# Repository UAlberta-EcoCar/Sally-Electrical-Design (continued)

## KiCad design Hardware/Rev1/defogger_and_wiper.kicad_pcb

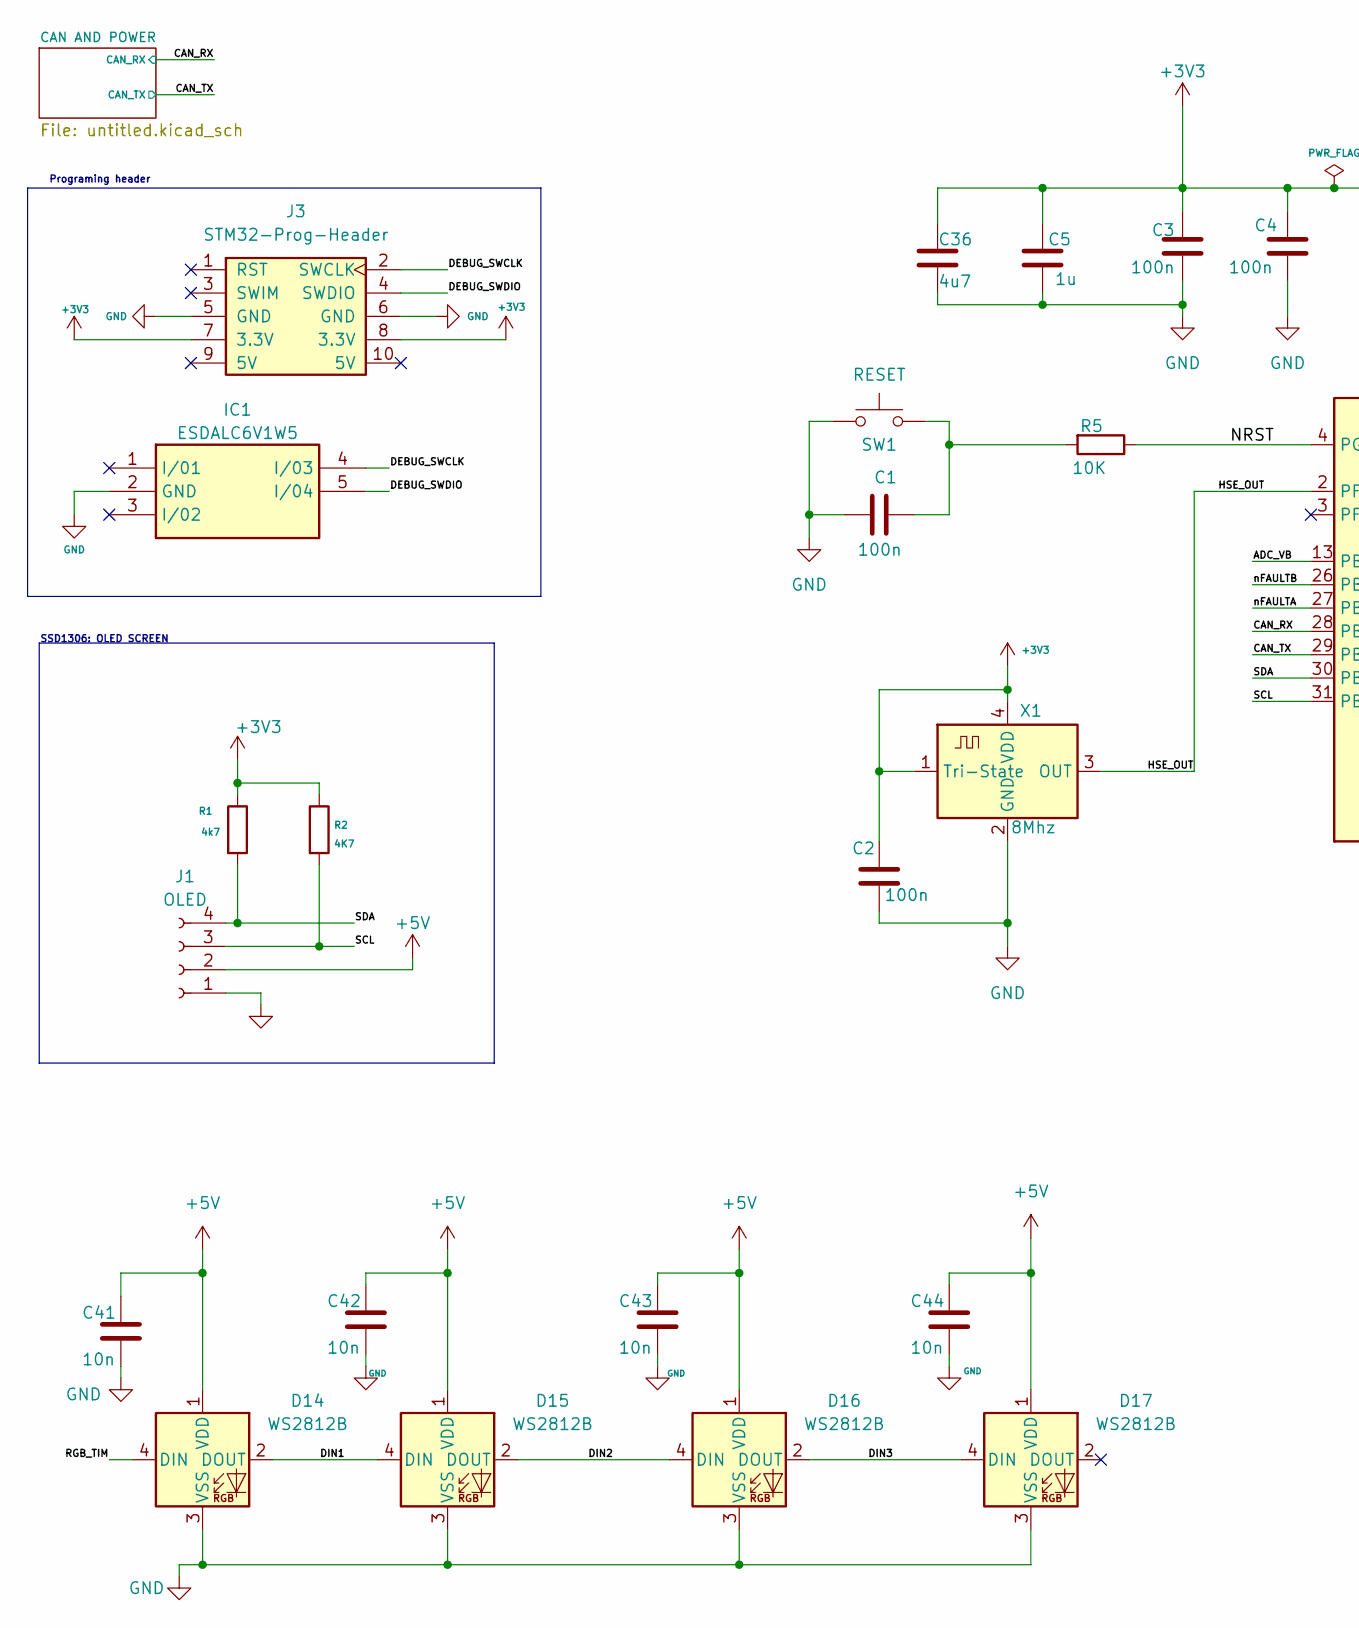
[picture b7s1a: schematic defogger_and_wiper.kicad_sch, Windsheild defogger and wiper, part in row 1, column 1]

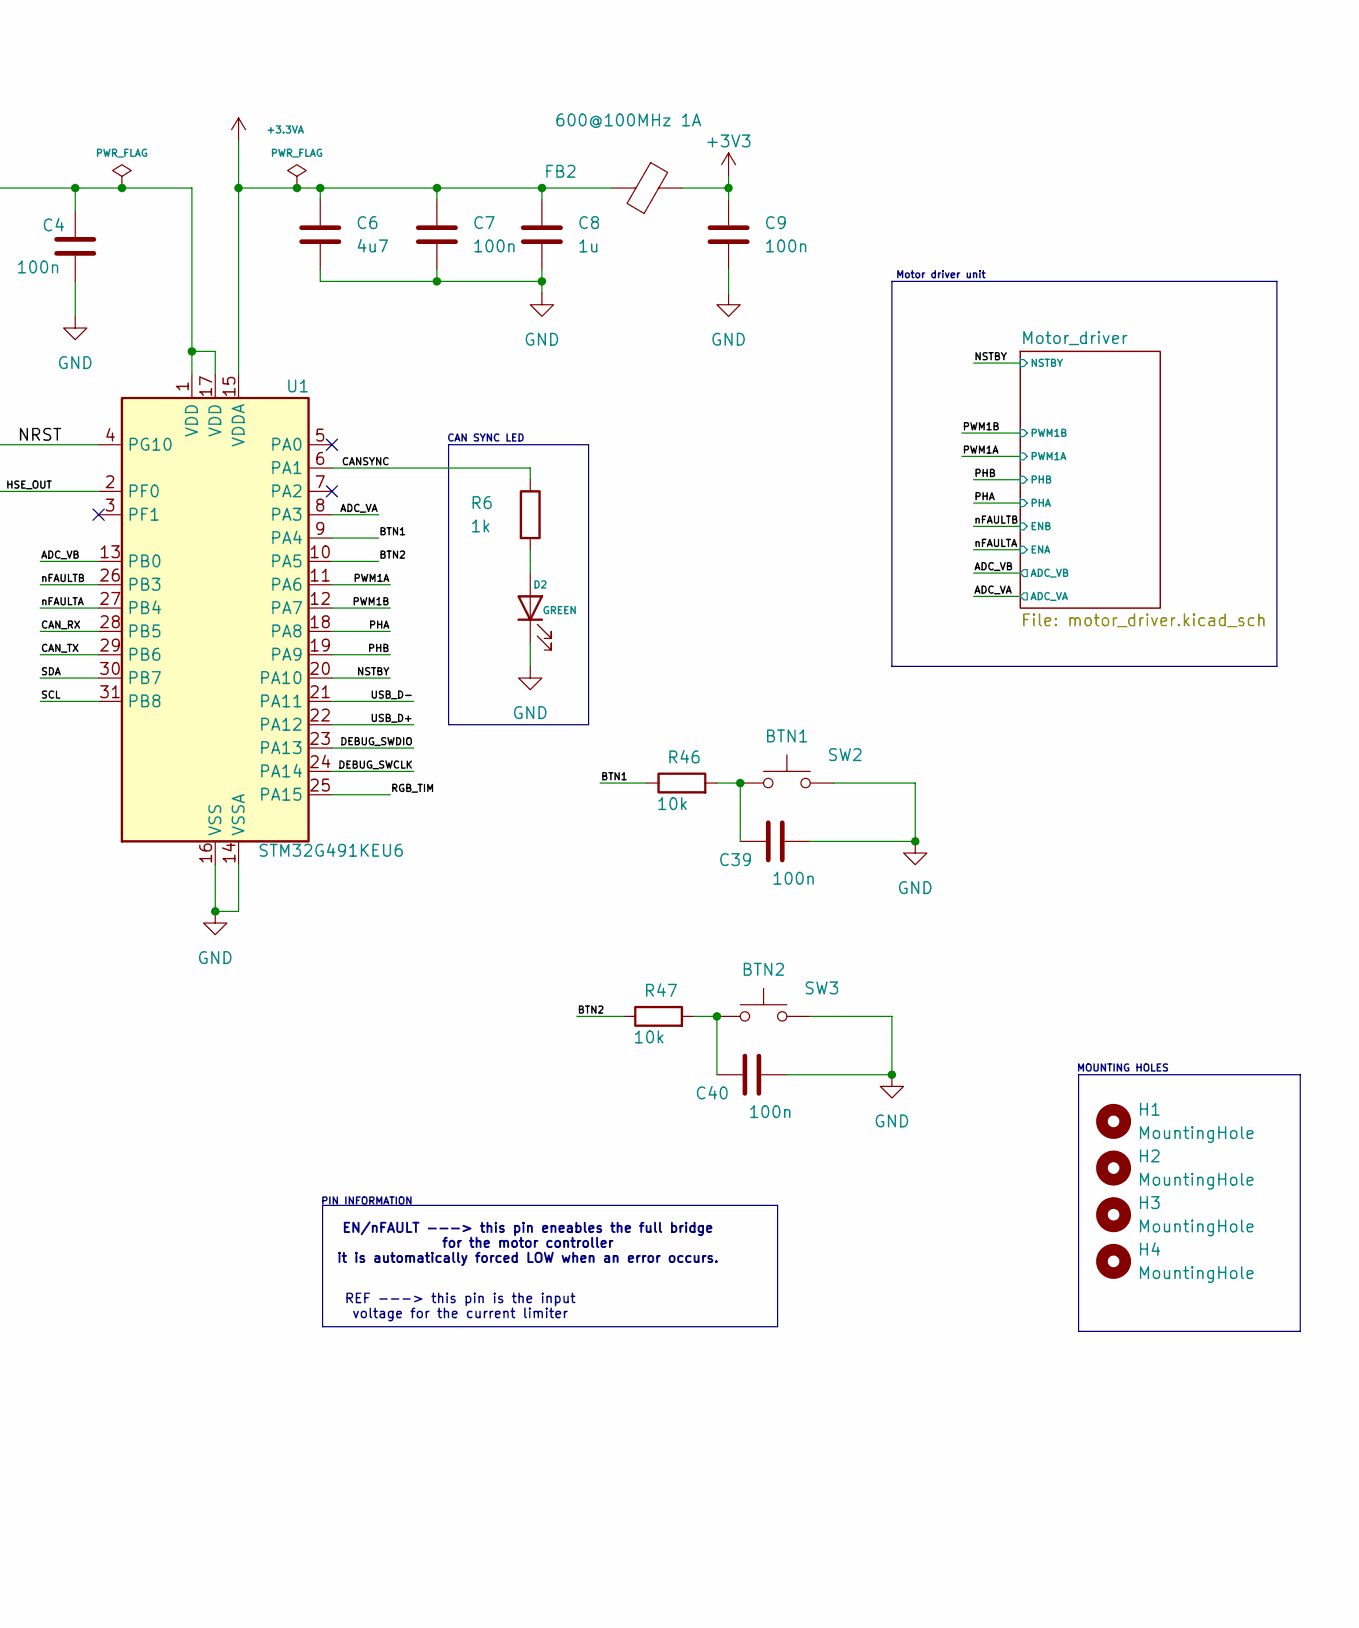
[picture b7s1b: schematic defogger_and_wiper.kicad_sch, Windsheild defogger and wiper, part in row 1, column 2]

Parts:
C1: 100n; C_0603_1608Metric; JLCPCB Part#(Optional) C1525
C2, C3, C4, C39, C40: 100n; C_0603_1608Metric
C5, C8: 1u; C_0603_1608Metric; JLCPCB Part#(Optional) C28323
C6, C36: 4u7; C_0603_1608Metric; JLCPCB Part#(Optional) C96446
C7: 100n; C_0603_1608Metric; JLCPCB Part#(Optional) C96446
C9: 100n; C_0603_1608Metric; JLCPCB Part#(Optional) C28323
C41, C42, C43, C44: 10n; C_0603_1608Metric; LCSC# C100042
D2: GREEN; LED_0603_1608Metric; LCSC# C19273151
D14, D15, D16, D17: WS2812B; LED_WS2812B_PLCC4_5.0x5.0mm_P3.2mm
FB2: 600@100MHz 1A; L_0603_1608Metric; Digikey # 1934-1474-1-ND
H1, H2, H3, H4: MountingHole; MountingHole_3.5mm
IC1: ESDALC6V1W5; SOT65P210X110-5N; JLCPCB Part#(Optional) C2827626
J1: OLED; Display_128x64_096_I2C
J3: STM32-Prog-Header; IDC-STM32-Prog-Header_2x05_P2.54mm_Vertical
R1: 4k7; R_0603_1608Metric
R2: 4K7; R_0603_1608Metric
R5: 10K; R_0603_1608Metric
R6: 1k; R_0603_1608Metric; LCSC# C21190
R46, R47: 10k; R_0603_1608Metric
SW1: RESET; SW_PUSH_6mm_H5mm
SW2: BTN1; SW_PUSH_6mm_H5mm
SW3: BTN2; SW_PUSH_6mm_H5mm
U1: STM32G491KEU6; QFN-32-1EP_5x5mm_P0.5mm_EP3.45x3.45mm
X1: 8Mhz; Crystal_SMD_3225-4Pin_3.2x2.5mm

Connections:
+3.3VA: C6.1, C7.1, C8.1, FB2.2, U1.15 (VDDA)
+3V3: C2.1, C3.1, C4.1, C5.1, C9.1, C36.1, FB2.1, J3.7 (3.3V), J3.8 (3.3V), R1.1, R2.1, U1.1 (VDD), U1.17 (VDD), X1.1 (Tri-State), X1.4 (VDD); also elsewhere on the board
+5V: C41.1, C42.1, C43.1, C44.1, D14.1 (VDD), D15.1 (VDD), D16.1 (VDD), D17.1 (VDD), J1.2; also elsewhere on the board
/ADC_VA: U1.8 (PA3); also elsewhere on the board
/ADC_VB: U1.13 (PB0); also elsewhere on the board
/BTN1: R46.1, U1.9 (PA4)
/BTN2: R47.1, U1.10 (PA5)
/CANSYNC: R6.1, U1.6 (PA1)
/CAN_RX: U1.28 (PB5); also elsewhere on the board
/CAN_TX: U1.29 (PB6); also elsewhere on the board
/DEBUG_SWCLK: IC1.4 (I/03), J3.2 (SWCLK), U1.24 (PA14)
/DEBUG_SWDIO: IC1.5 (I/04), J3.4 (SWDIO), U1.23 (PA13)
/DIN1: D14.2 (DOUT), D15.4 (DIN)
/DIN2: D15.2 (DOUT), D16.4 (DIN)
/DIN3: D16.2 (DOUT), D17.4 (DIN)
/HSE_OUT: U1.2 (PF0), X1.3 (OUT)
/NRST: R5.1, U1.4 (PG10)
/NSTBY: U1.20 (PA10); also elsewhere on the board
/PHA: U1.18 (PA8); also elsewhere on the board
/PHB: U1.19 (PA9); also elsewhere on the board
/PWM1A: U1.11 (PA6); also elsewhere on the board
/PWM1B: U1.12 (PA7); also elsewhere on the board
/RGB_TIM: D14.4 (DIN), U1.25 (PA15)
/SCL: J1.3, R2.2, U1.31 (PB8)
/SDA: J1.4, R1.2, U1.30 (PB7)
/USB_D+: U1.22 (PA12)
/USB_D-: U1.21 (PA11)
/nFAULTA: U1.27 (PB4); also elsewhere on the board
/nFAULTB: U1.26 (PB3); also elsewhere on the board
GND: C1.1, C2.2, C3.2, C4.2, C5.2, C6.2, C7.2, C8.2, C9.2, C36.2, C39.2, C40.2, C41.2, C42.2, C43.2, C44.2, D2.1 (K), D14.3 (VSS), D15.3 (VSS), D16.3 (VSS), D17.3 (VSS), IC1.2 (GND), J1.1, J3.5 (GND), J3.6 (GND), SW1.1, SW2.2, SW3.2, U1.14 (VSSA), U1.16 (VSS), U1.32 (VSS), U1.33 (VSS), X1.2 (GND); also elsewhere on the board
unnamed: C1.2, R5.2, SW1.2
unnamed: C39.1, R46.2, SW2.1
unnamed: C40.1, R47.2, SW3.1
unnamed: D2.2 (A), R6.2

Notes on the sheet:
PIN INFORMATION
EN/nFAULT ---> this pin eneables the full bridge for the motor controller it is automatically forced LOW when an error occurs.
Programing header
SSD1306: OLED SCREEN
CAN SYNC LED
Motor driver unit
MOUNTING HOLES
REF ---> this pin is the input voltage for the current limiter

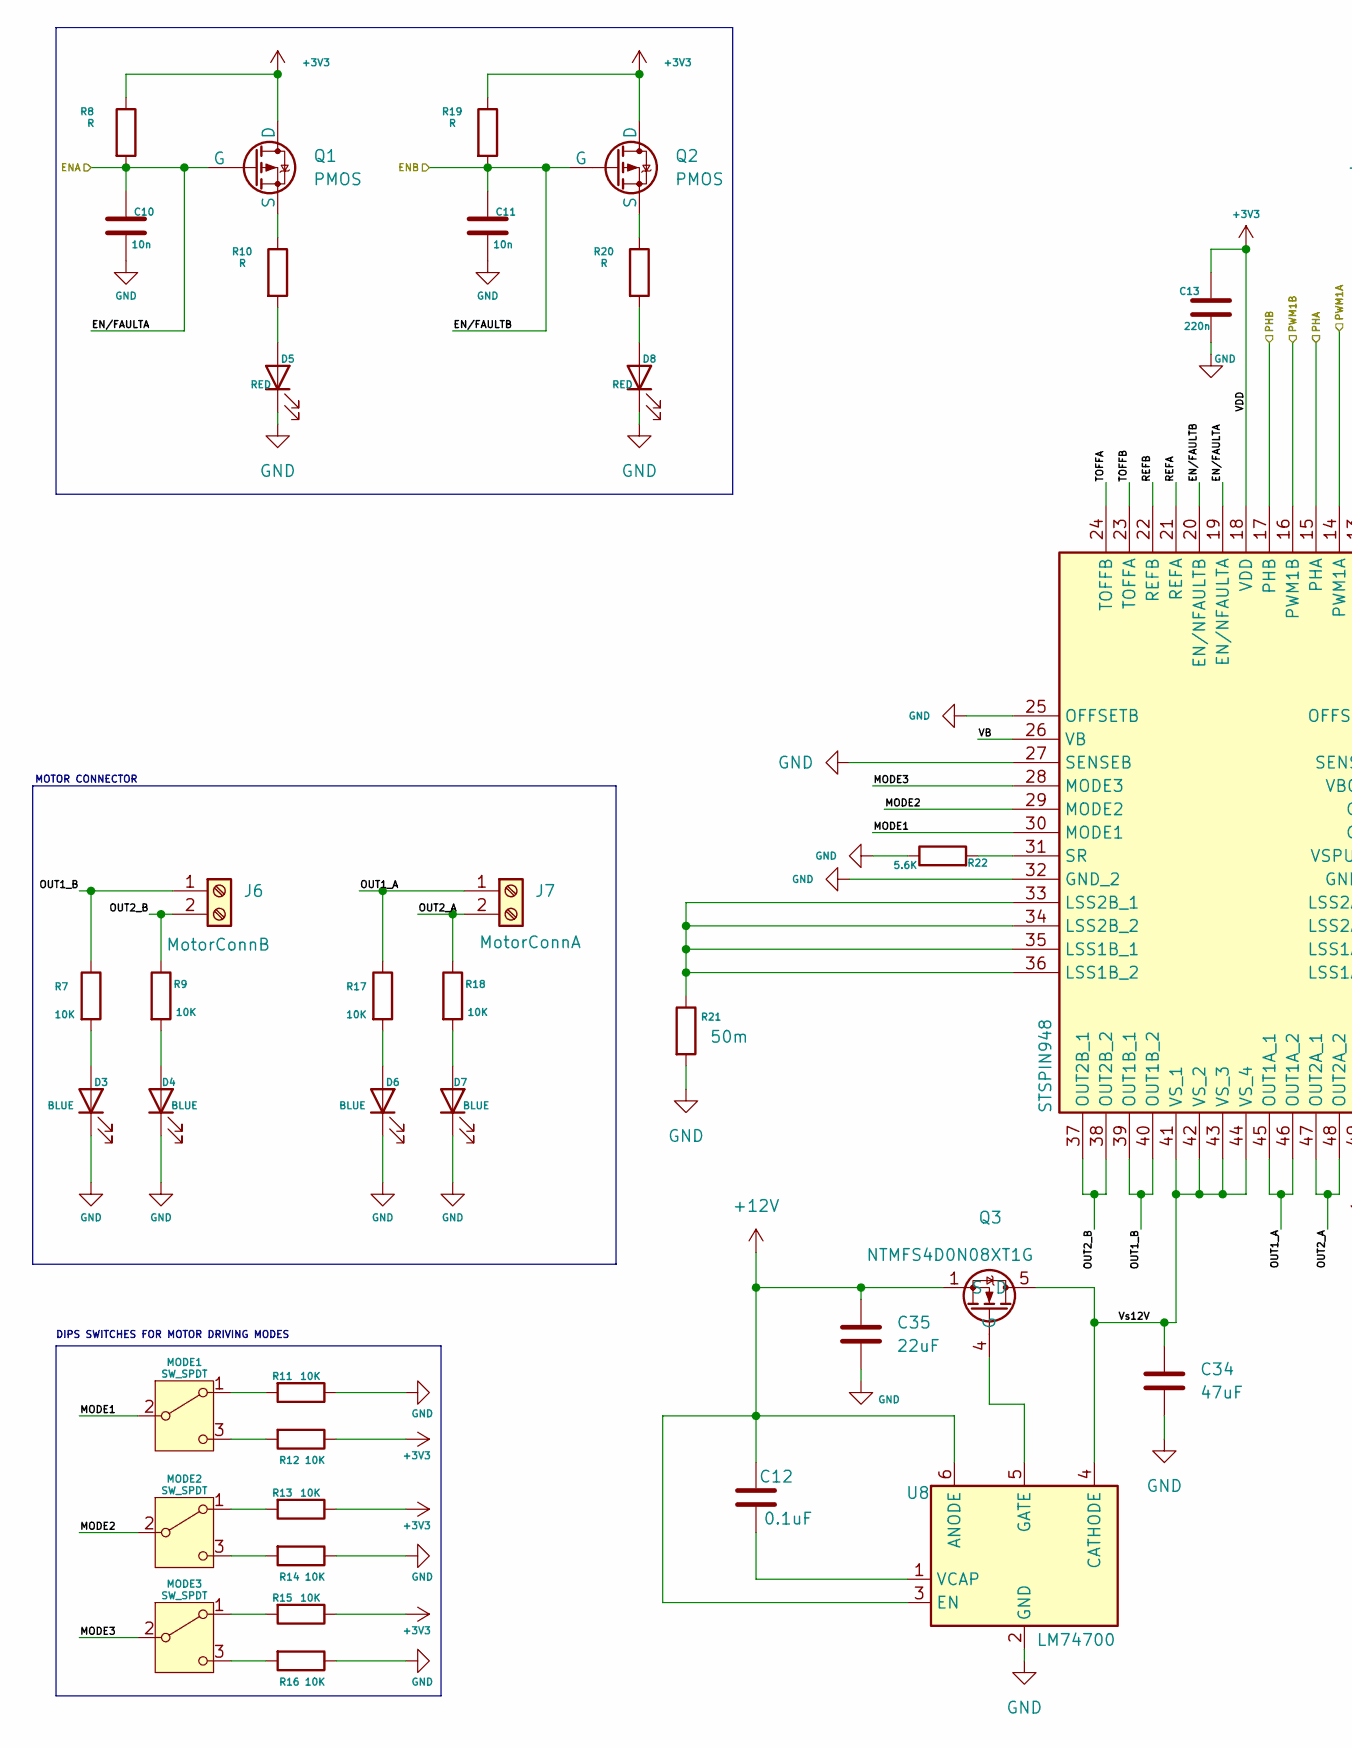
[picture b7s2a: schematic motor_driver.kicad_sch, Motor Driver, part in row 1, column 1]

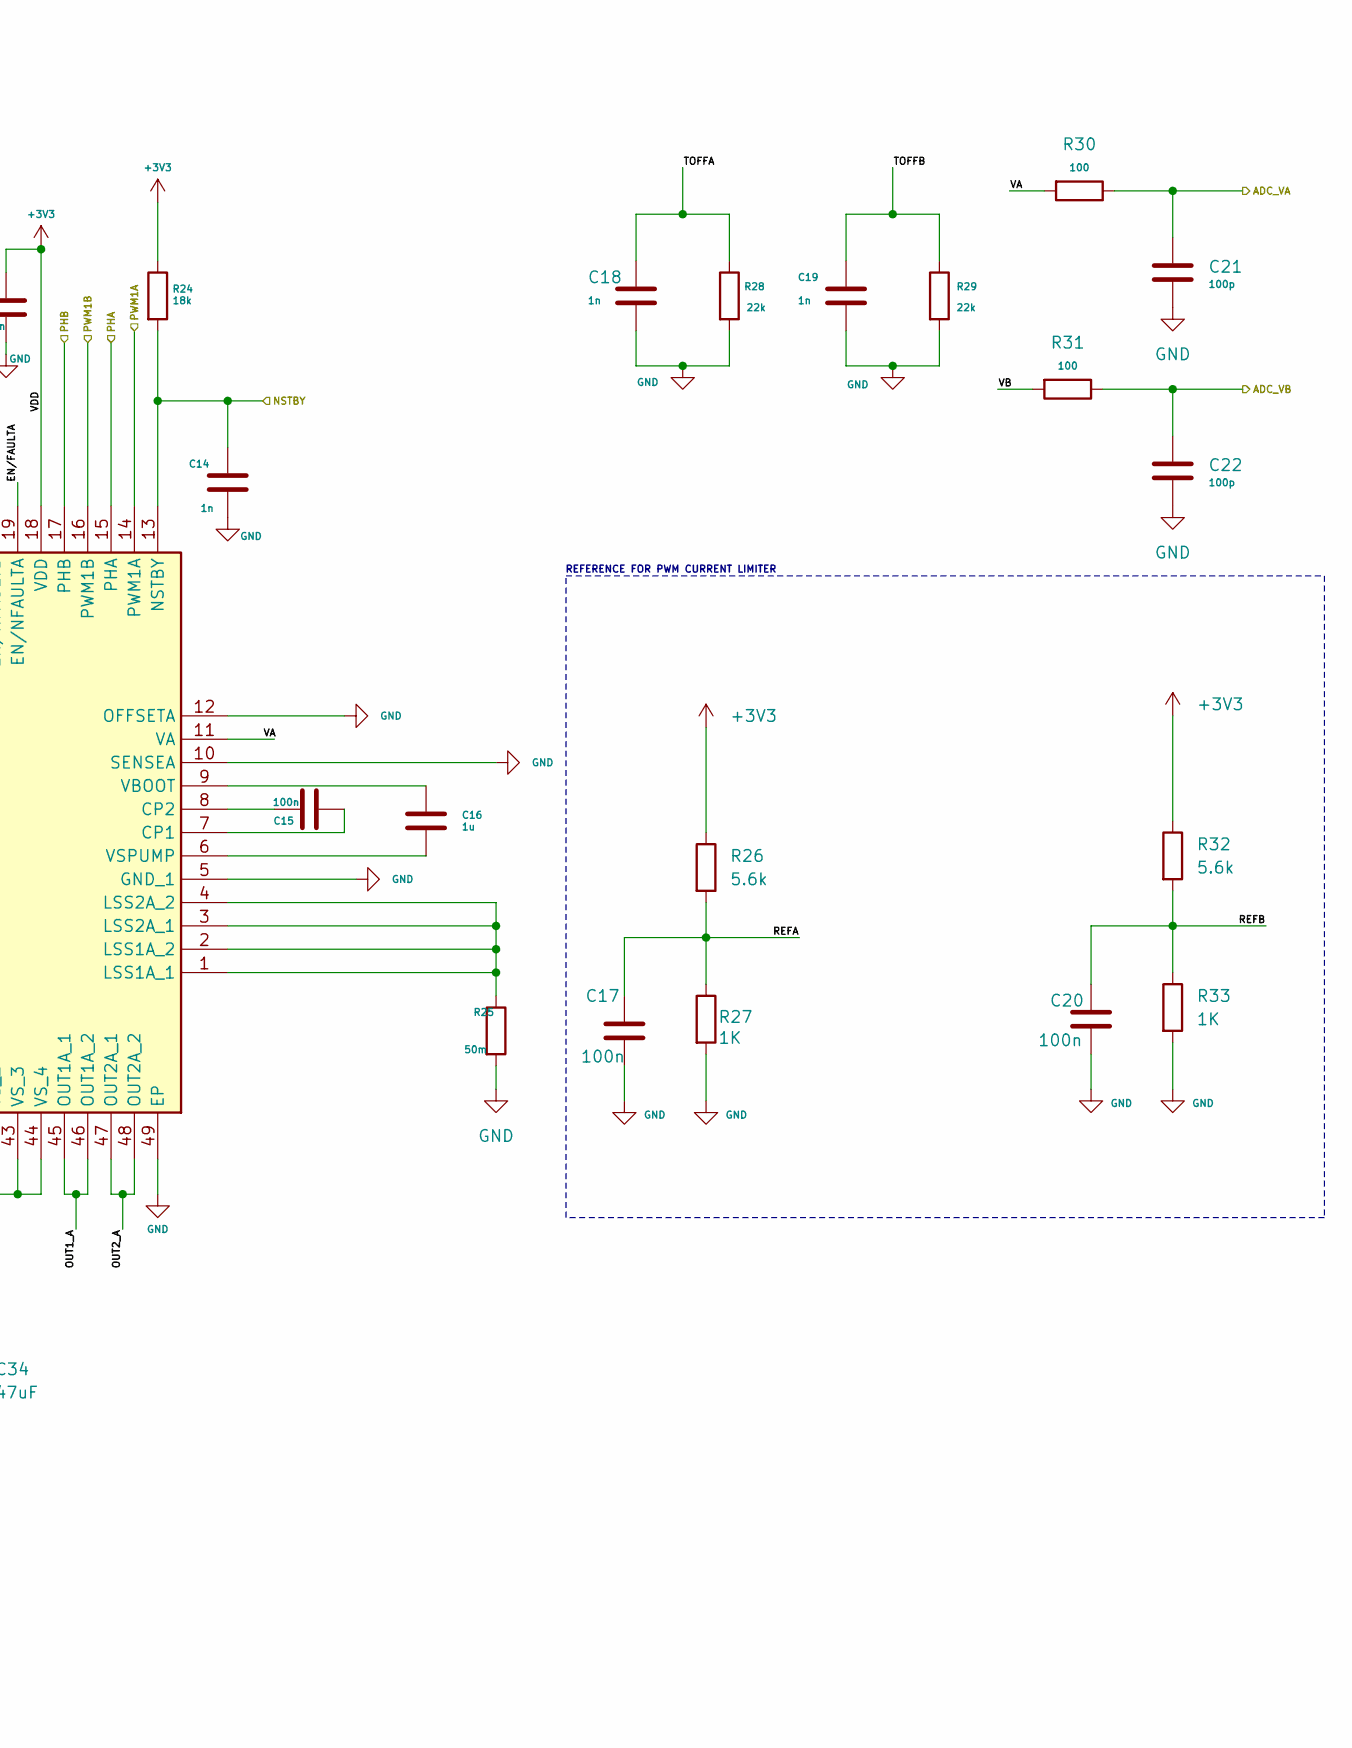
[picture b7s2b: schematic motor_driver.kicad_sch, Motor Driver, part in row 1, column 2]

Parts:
C10, C11: 10n; C_0603_1608Metric; LCSC# C100042
C12: 0.1uF; C_0603_1608Metric
C13: 220n; C_0603_1608Metric
C14, C18, C19: 1n; C_0603_1608Metric
C15, C17, C20: 100n; C_0603_1608Metric
C16: 1u; C_0603_1608Metric
C21, C22: 100p; C_0603_1608Metric
C34: 47uF; C_0603_1608Metric
C35: 22uF; C_0603_1608Metric
D3, D4, D6, D7: BLUE; LED_0603_1608Metric; LCSC# C19171394
D5, D8: RED; LED_0603_1608Metric; LCSC# C19171390
IC2: STSPIN948; QFN50P700X700X105-49N-D; Manufacturer_Part_Number STSPIN948; Mouser Part Number 511-STSPIN948
J6: MotorConnB; TerminalBlock_Phoenix_MKDS-1,5-2-5.08_1x02_P5.08mm_Horizont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
J7: MotorConnA; TerminalBlock_Phoenix_MKDS-1,5-2-5.08_1x02_P5.08mm_Horizont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
MODE1, MODE2, MODE3: SW_SPDT; SW_SPDT_PCM12
Q1, Q2: PMOS; SOT-23_TO-236_318-AT_OSI
Q3: NTMFS4D0N08XT1G; PowerMosDFNHybrid
R7, R9, R11, R12, R13, R14, R15, R16, R17, R18: 10K; R_0603_1608Metric
R8, R10, R19, R20: R; R_0603_1608Metric
R21: 50m; R_1812_4532Metric
R22: 5.6K; R_0603_1608Metric
R24: 18k; R_0603_1608Metric
R25: 50m; R_0603_1608Metric
R26, R32: 5.6k; R_0603_1608Metric
R27, R33: 1K; R_0603_1608Metric
R28, R29: 22k; R_0603_1608Metric
R30, R31: 100; R_0603_1608Metric
U8: LM74700; SOT-23-6

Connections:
+3V3: C13.1, IC2.18 (VDD), Q1.1 (D), Q2.1 (D), R8.1, R12.1, R13.1, R15.1, R19.1, R24.1, R26.1, R32.1; also elsewhere on the board
+12V: C12.1, C35.1, Q3.1 (S), Q3.2 (S), Q3.3 (S), U8.3 (EN), U8.6 (ANODE); also elsewhere on the board
/ADC_VA: C21.1, R30.1; also elsewhere on the board
/ADC_VB: C22.1, R31.1; also elsewhere on the board
/Motor_driver/MODE1: IC2.30 (MODE1), MODE1.2 (B)
/Motor_driver/MODE2: IC2.29 (MODE2), MODE2.2 (B)
/Motor_driver/MODE3: IC2.28 (MODE3), MODE3.2 (B)
/Motor_driver/OUT1_A: IC2.45 (OUT1A_1), IC2.46 (OUT1A_2), J7.1, R17.1
/Motor_driver/OUT1_B: IC2.39 (OUT1B_1), IC2.40 (OUT1B_2), J6.1, R7.1
/Motor_driver/OUT2_A: IC2.47 (OUT2A_1), IC2.48 (OUT2A_2), J7.2, R18.1
/Motor_driver/OUT2_B: IC2.37 (OUT2B_1), IC2.38 (OUT2B_2), J6.2, R9.1
/Motor_driver/REFA: C17.1, IC2.21 (REFA), R26.2, R27.1
/Motor_driver/REFB: C20.1, IC2.22 (REFB), R32.2, R33.1
/Motor_driver/TOFFA: C18.2, IC2.24 (TOFFB), R28.1
/Motor_driver/TOFFB: C19.2, IC2.23 (TOFFA), R29.1
/Motor_driver/VA: IC2.11 (VA), R30.2
/Motor_driver/VB: IC2.26 (VB), R31.2
/Motor_driver/Vs12V: C34.1, IC2.41 (VS_1), IC2.42 (VS_2), IC2.43 (VS_3), IC2.44 (VS_4), Q3.5 (D), U8.4 (CATHODE)
/NSTBY: C14.1, IC2.13 (NSTBY), R24.2; also elsewhere on the board
/PHA: IC2.15 (PHA); also elsewhere on the board
/PHB: IC2.17 (PHB); also elsewhere on the board
/PWM1A: IC2.14 (PWM1A); also elsewhere on the board
/PWM1B: IC2.16 (PWM1B); also elsewhere on the board
/nFAULTA: C10.1, IC2.19 (EN/NFAULTA), Q1.2 (G), R8.2; also elsewhere on the board
/nFAULTB: C11.1, IC2.20 (EN/NFAULTB), Q2.2 (G), R19.2; also elsewhere on the board
GND: C10.2, C11.2, C13.2, C14.2, C17.2, C18.1, C19.1, C20.2, C21.2, C22.2, C34.2, C35.2, D3.1 (K), D4.1 (K), D5.1 (K), D6.1 (K), D7.1 (K), D8.1 (K), IC2.5 (GND_1), IC2.10 (SENSEA), IC2.12 (OFFSETA), IC2.25 (OFFSETB), IC2.27 (SENSEB), IC2.32 (GND_2), IC2.49 (EP), R11.1, R14.1, R16.1, R21.2, R22.1, R25.2, R27.2, R28.2, R29.2, R33.2, U8.2 (GND); also elsewhere on the board
unnamed: D3.2 (A), R7.2
unnamed: D4.2 (A), R9.2
unnamed: D5.2 (A), R10.2
unnamed: D6.2 (A), R17.2
unnamed: D7.2 (A), R18.2
unnamed: D8.2 (A), R20.2
unnamed: C15.1, IC2.7 (CP1)
unnamed: C15.2, IC2.8 (CP2)
unnamed: IC2.1 (LSS1A_1), IC2.2 (LSS1A_2), IC2.3 (LSS2A_1), IC2.4 (LSS2A_2), R25.1
unnamed: IC2.33 (LSS2B_1), IC2.34 (LSS2B_2), IC2.35 (LSS1B_1), IC2.36 (LSS1B_2), R21.1
unnamed: IC2.31 (SR), R22.2
unnamed: C16.1, IC2.9 (VBOOT)
unnamed: C16.2, IC2.6 (VSPUMP)
unnamed: MODE1.1 (A), R11.2
unnamed: MODE1.3 (C), R12.2
unnamed: MODE2.1 (A), R13.2
unnamed: MODE2.3 (C), R14.2
unnamed: MODE3.1 (A), R15.2
unnamed: MODE3.3 (C), R16.2
unnamed: Q1.3 (S), R10.1
unnamed: Q2.3 (S), R20.1
unnamed: Q3.4 (G), U8.5 (GATE)
unnamed: C12.2, U8.1 (VCAP)

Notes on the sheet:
MOTOR CONNECTOR
DIPS SWITCHES FOR MOTOR DRIVING MODES
REFERENCE FOR PWM CURRENT LIMITER

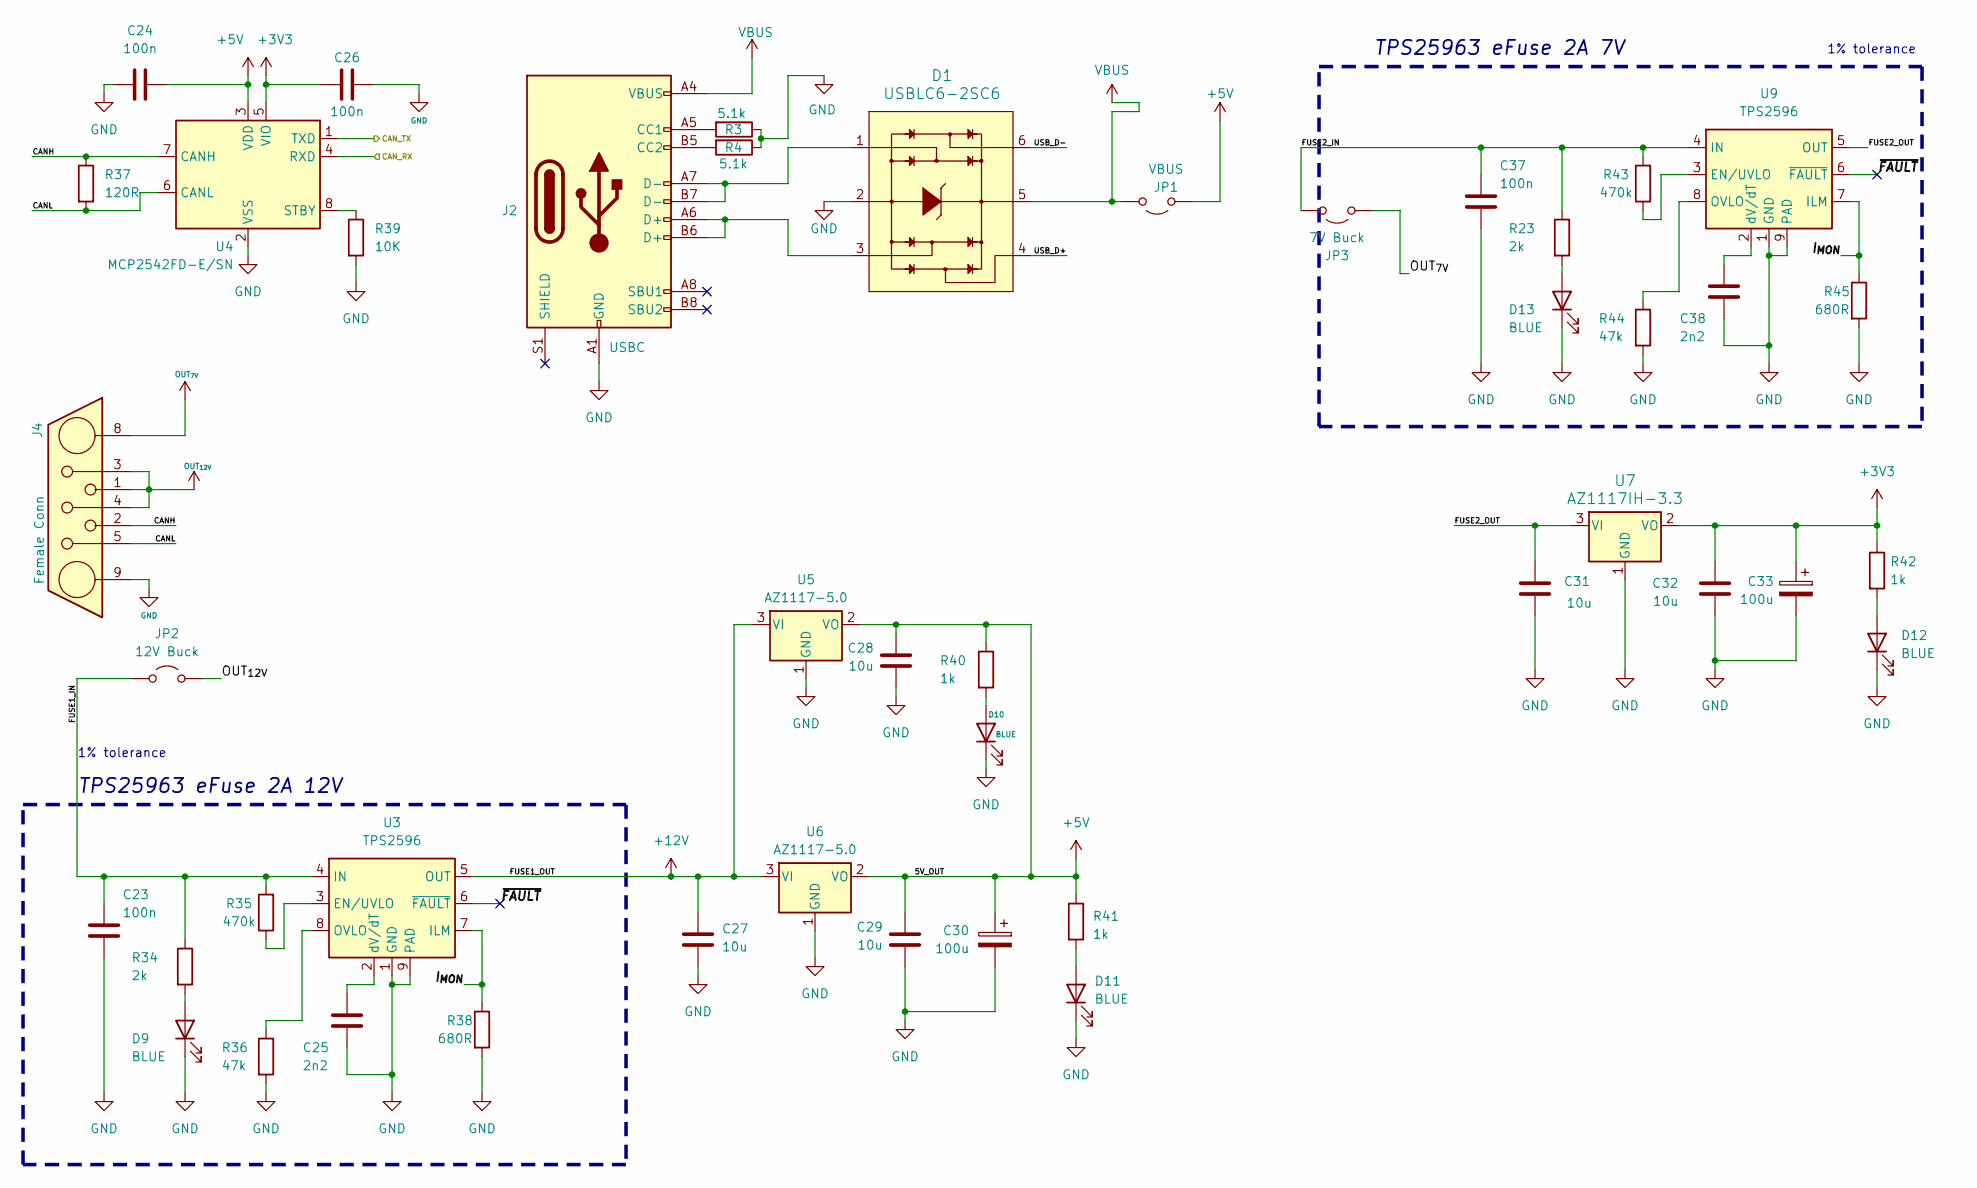
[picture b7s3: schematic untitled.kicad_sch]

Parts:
C23, C37: 100n; C_0603_1608Metric; JLCPCB Part#(Optional) C28233
C24, C26: 100n; C_0603_1608Metric; JLCPCB Part#(Optional) C1525
C25, C38: 2n2; C_0603_1608Metric; JLCPCB Part#(Optional) C1531
C27, C28, C29, C31, C32: 10u; C_0805_2012Metric; LCSC# C15850
C30, C33: 100u; CP_Elec_6.3x9.9; LCSC# C72478
D1: USBLC6-2SC6; TSOT-23-6; Digikey # 497-5235-1-ND
D9, D10, D11, D12, D13: BLUE; LED_0603_1608Metric; LCSC# C19171394
J2: USBC; USB_C_Receptacle_GCT_USB4105-xx-A_16P_TopMnt_Horizontal
J4: Female Conn; DB7W2-Female
JP1: VBUS; J_0603_Triangular
JP2: 12V Buck; J_0603_Triangular
JP3: 7V Buck; J_0603_Triangular
R3, R4: 5.1k; R_0603_1608Metric; JLCPCB Part#(Optional) C17557
R23, R34: 2k; R_0603_1608Metric; JLCPCB Part#(Optional) C17604
R35, R43: 470k; R_0603_1608Metric; JLCPCB Part#(optional) C17709
R36, R44: 47k; R_0603_1608Metric; JLCPCB Part#(optional) C17713
R37: 120R; R_0603_1608Metric
R38, R45: 680R; R_0603_1608Metric; JLCPCB Part#(Optional) C23220
R39: 10K; R_0603_1608Metric
R40, R41, R42: 1k; R_0603_1608Metric; LCSC# C21190
U3, U9: TPS2596; TI_SO-PowerPAD-8
U4: MCP2542FD-E/SN; SOIC-8_3.9x4.9mm_P1.27mm; Digikey # MCP2542FD-E/SN-ND
U5, U6: AZ1117-5.0; SOT-223-3_TabPin2
U7: AZ1117IH-3.3; SOT-223-3_TabPin2

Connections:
+3V3: C26.2, C32.1, C33.1, R42.1, U4.5 (VIO), U7.2 (VO); also elsewhere on the board
+5V: C24.2, C28.1, C29.1, C30.1, JP1.1 (A), R40.1, R41.1, U4.3 (VDD), U5.2 (VO), U6.2 (VO); also elsewhere on the board
+12V: C27.1, U3.5 (OUT), U5.3 (VI), U6.3 (VI); also elsewhere on the board
/CAN AND POWER/CANH: J4.2, R37.1, U4.7 (CANH)
/CAN AND POWER/CANL: J4.5, R37.2, U4.6 (CANL)
/CAN AND POWER/FUSE1_IN: C23.1, JP2.1 (A), R34.1, R35.2, U3.4 (IN)
/CAN AND POWER/FUSE2_IN: C37.1, JP3.1 (A), R23.1, R43.2, U9.4 (IN)
/CAN AND POWER/FUSE2_OUT: C31.1, U7.3 (VI), U9.5 (OUT)
/CAN AND POWER/I_{MON}: R38.1, R45.1, U3.7 (ILM), U9.7 (ILM)
/CAN AND POWER/USB_D+: D1.4
/CAN AND POWER/USB_D-: D1.6
/CAN AND POWER/~FAULT: U3.6 (~FAULT), U9.6 (~FAULT)
/CAN_RX: U4.4 (RXD); also elsewhere on the board
/CAN_TX: U4.1 (TXD); also elsewhere on the board
GND: C23.2, C24.1, C25.2, C26.1, C27.2, C28.2, C29.2, C30.2, C31.2, C32.2, C33.2, C37.2, C38.2, D1.2, D9.1 (K), D10.1 (K), D11.1 (K), D12.1 (K), D13.1 (K), J2.A1 (GND), J2.A12 (GND), J2.B1 (GND), J2.B12 (GND), J4.9, R3.1, R4.1, R36.2, R38.2, R39.2, R44.2, R45.2, U3.1 (GND), U3.9 (PAD), U4.2 (VSS), U4.9 (VSS), U5.1 (GND), U6.1 (GND), U7.1 (GND), U9.1 (GND), U9.9 (PAD); also elsewhere on the board
unnamed: D1.1, J2.A7 (D-), J2.B7 (D-)
unnamed: D1.3, J2.A6 (D+), J2.B6 (D+)
unnamed: D9.2 (A), R34.2
unnamed: D10.2 (A), R40.2
unnamed: D11.2 (A), R41.2
unnamed: D12.2 (A), R42.2
unnamed: D13.2 (A), R23.2
unnamed: J2.A5 (CC1), R3.2
unnamed: J2.B5 (CC2), R4.2
unnamed: R35.1, U3.3 (EN/UVLO)
unnamed: R36.1, U3.8 (OVLO)
unnamed: C25.1, U3.2 (dV/dT)
unnamed: R39.1, U4.8 (STBY)
unnamed: R43.1, U9.3 (EN/UVLO)
unnamed: R44.1, U9.8 (OVLO)
unnamed: C38.1, U9.2 (dV/dT)
OUT_{7V}: J4.8, JP3.2 (B)
OUT_{12V}: J4.1, J4.3, J4.4, JP2.2 (B)
VBUS: D1.5, J2.A4 (VBUS), J2.A9 (VBUS), J2.B4 (VBUS), J2.B9 (VBUS), JP1.2 (B)

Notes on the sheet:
TPS25963 eFuse 2A 12V
1% tolerance
TPS25963 eFuse 2A 7V

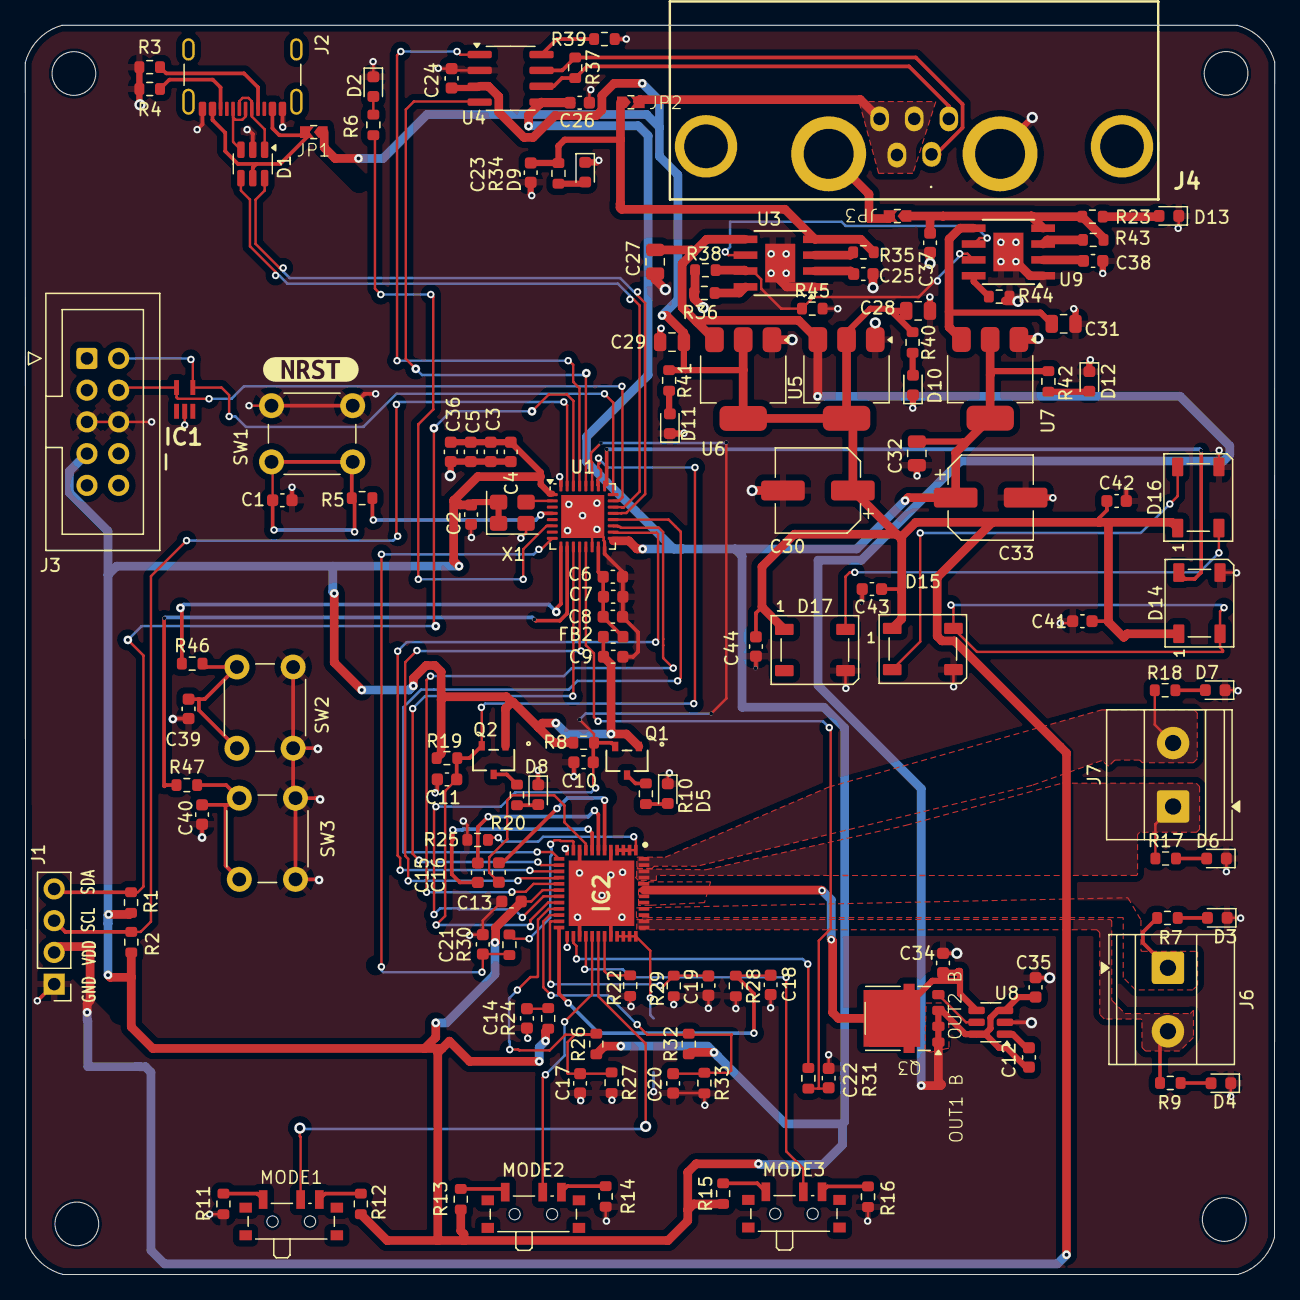
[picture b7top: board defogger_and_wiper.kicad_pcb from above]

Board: 4 copper layers, 100.0 x 100.0 mm, 143 parts (1 on the bottom side), 96 nets.

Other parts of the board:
kibuzzard-696D2580: G***; kibuzzard-696D2580

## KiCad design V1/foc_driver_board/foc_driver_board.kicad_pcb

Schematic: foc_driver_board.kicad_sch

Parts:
C1, C3, C5, C7: 22u; C_0603_1608Metric
C2, C4, C8, C9, C10, C14, C15, C16, C17, C18, C19: 0u1; C_0603_1608Metric
C6, C13: 1u; C_0603_1608Metric
C11: 4u7; C_0603_1608Metric
C12: 10n; C_0603_1608Metric
D1: ESDALC6V1P5
FB1: FerriteBead; L_0603_1608Metric
H1, H2, H3, H4: MountingHole; MountingHole_3.2mm_M3
J1: STM32-Prog-Header; IDC-STM32-Prog-Header_2x05_P2.54mm_Vertical
J2, J5: Conn_01x02_Pin; PinSocket_1x02_P2.54mm_Vertical
J3: Conn_01x06_Pin; STD_PWR_HEADER
J4: Conn_01x18; ILI9488
LED1, LED2, LED3, LED4, LED5: COM-16347; COM-16347_SPK
R1: 120R; R_0603_1608Metric
R2, R3, R4: 10k; R_0603_1608Metric
SW1: SW_Push; SW_PUSH_6mm
U2: AZ1117IH-3.3; SOT-223-3_TabPin2
U3: AZ1117IH-5.0; SOT-223-3_TabPin2
U4: MCP2542FD; SOIC-8_3.9x4.9mm_P1.27mm
U5: STM32G491KEUx; QFN-32-1EP_5x5mm_P0.5mm_EP3.45x3.45mm
U6: MCP6007; SOIC-8_3.9x4.9mm_P1.27mm
X1: OXETDLJANF-8MHZ; Crystal_SMD_3225-4Pin_3.2x2.5mm

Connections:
+3.3V: C2.1, C3.1, C4.1, C8.1, C10.1, C11.1, FB1.1, J1.7 (3.3V), J1.8 (3.3V), R3.1, U2.2 (VO), U4.5 (VIO), U5.1 (VDD), U5.17 (VDD), X1.1 (Tri-State), X1.4 (VDD)
+3.3VA: C12.1, C13.1, FB1.2, U5.15 (VDDA)
+5V: C6.1, C7.1, C14.1, C15.1, C16.1, C17.1, C18.1, C19.1, J4.1, LED1.1 (VDD), LED2.1 (VDD), LED3.1 (VDD), LED4.1 (VDD), LED5.1 (VDD), U3.2 (VO), U4.3 (VDD), U6.8 (V+)
+12V: C5.1, J3.3, J3.6, U3.3 (VI)
/BOOT: R2.1, U5.31 (PB8)
/CAN_N: J3.2, R1.1, U4.6 (CANL)
/CAN_P: J3.1, R1.2, U4.7 (CANH)
/DIN1: LED1.4 (DIN), U6.1
/DIN2: LED1.2 (DOUT), LED2.4 (DIN)
/DIN3: LED2.2 (DOUT), LED3.4 (DIN)
/DIN4: LED3.2 (DOUT), LED4.4 (DIN)
/DIN5: LED4.2 (DOUT), LED5.4 (DIN)
/FDCAN_RX: U4.4 (RXD), U5.28 (PB5)
/FDCAN_STBY: U4.8 (STBY), U5.30 (PB7)
/FDCAN_TX: U4.1 (TXD), U5.29 (PB6)
/LCD_BRIGHT: J4.8, U5.7 (PA2)
/LCD_CS: J4.3, U5.9 (PA4)
/LCD_DC/RS: J4.5, U5.8 (PA3)
/LCD_RESET: J4.4, U5.13 (PB0)
/LED_{SET}: U5.5 (PA0), U6.3 (+)
/PA1: U5.6 (PA1)
/PA10: U5.20 (PA10)
/PA15: U5.25 (PA15)
/PB3: J2.1, U5.26 (PB3)
/PB4: J5.1, U5.27 (PB4)
/PF1: U5.3 (PF1)
/RCC: U5.2 (PF0), X1.3 (OUT)
/SPI_MISO: J4.9, J4.13, U5.11 (PA6)
/SPI_MOSI: J4.6, J4.12, U5.12 (PA7)
/SPI_SCK: J4.7, J4.10, U5.10 (PA5)
/SWCLK: D1.5, J1.2 (SWCLK), U5.24 (PA14)
/SWDIO: D1.4, J1.4 (SWDIO), U5.23 (PA13)
/T_CS: J4.11, U5.19 (PA9)
/T_IRQ: J4.14, U5.18 (PA8)
/USB_N: U5.21 (PA11)
/USB_P: U5.22 (PA12)
/nRST: C9.1, SW1.2, U5.4 (PG10)
GNDA: C1.2, C2.2, C3.2, C4.2, C5.2, C6.2, C7.2, C8.2, C9.2, C10.2, C11.2, C12.2, C13.2, C14.2, C15.2, C16.2, C17.2, C18.2, C19.2, D1.2, J1.5 (GND), J1.6 (GND), J2.2, J3.5, J4.2, J5.2, LED1.3 (VSS), LED2.3 (VSS), LED3.3 (VSS), LED4.3 (VSS), LED5.2 (DOUT), LED5.3 (VSS), R2.2, R4.2, SW1.1, U2.1 (GND), U3.1 (GND), U4.2 (VSS), U5.14 (VSSA), U5.16 (VSS), U5.32 (VSS), U5.33 (VSS), U6.4 (V-), X1.2 (GND)
unnamed: R3.2, R4.1, U6.2 (-)
VCC: C1.1, J3.4, U2.3 (VI)

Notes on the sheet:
Logic shift from 3.3 to 5
7V Input
Module has onboard 5V -> 3.3V reg Logic is 3.3V
